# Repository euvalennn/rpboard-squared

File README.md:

# RPBoard²

RPBoard² is a simple RP2350-based board with multiple convenient features built-in. It's my first "actual" PCB project (I only did a hackpad before)

## Motivation

I wanted to build a devboard to learn more about actual PCB design and electronics, instead of using pre-made boards. I considered it as a personal challenge and ended up learning a lot on the two weeks it took me to make it :D

## Features:

- RP2350A MCU
- JST Debug header
- Built-in lithium battery support
- microSD card reader
- On-board RGB LED on GPIO25 (neopixel)
- QWIIC / Stemma QT I2C connector
- USB-C connector
- 16MB flash memory

## Built project:

| Front                                     | Back                                     |
| ----------------------------------------- | ---------------------------------------- |
|  |  |

## PCB and schematic:

### Schematic:

### PCB:

| PCB editor                                          | 3D viewer                                        |
| --------------------------------------------------- | ------------------------------------------------ |
|  |  |

Both the PCB and the schematic were designed using KiCad. The PCB is a 2-layer board with a ground pour on both layers.

## BOM:

| Name                             | Description                                                                                                                                            | Quantity | LCSC Part # | Total price |
| -------------------------------- | ------------------------------------------------------------------------------------------------------------------------------------------------------ | -------- | ----------- | ----------- |
| CL05A106MP5NUNC                  | 10V 10uF X5R ±20% 0402 Multilayer Ceramic Capacitors MLCC - SMD/SMT ROHS                                                                               | 4        | C315248     | $0.1640     |
| CGA0402X7R104K160GT              | 16V 100nF X7R ±10% 0402 Multilayer Ceramic Capacitors MLCC - SMD/SMT ROHS                                                                              | 13       | C6119799    | $0.0342     |
| CL05A475MP5NRNC                  | 10V 4.7uF X5R ±20% 0402 Multilayer Ceramic Capacitors MLCC - SMD/SMT ROHS                                                                              | 4        | C23733      | $0.0384     |
| CC0402JRNPO9BN150                | 50V 15pF NP0 ±5% 0402 Multilayer Ceramic Capacitors MLCC - SMD/SMT ROHS                                                                                | 2        | C106997     | $0.0220     |
| XL-1608SURC-06                   | 20mA 225mcd Water Clear op View Mount 620nm~630nm Red 120° 50mW 2.3V 0603 LED Indication - Discrete ROHS                                               | 1        | C965799     | $0.0620     |
| SK6812MINI-HS                    | SMD,3.5x3.7mm RGB LEDs(Built-in IC) ROHS                                                                                                               | 1        | C2922787    | $0.4665     |
| 1N5819WS                         | 40V 600mV@1A 1A SOD-323 Schottky Diodes ROHS                                                                                                           | 1        | C191023     | $0.0192     |
| TYPE-C-31-M-12                   | 5A 1 16P Female Type-C SMD USB Connectors ROHS                                                                                                         | 1        | C165948     | $0.3394     |
| BM03B-SRSS-TB(LF)(SN)            | 1x3P 3P SH Tin 3 -25℃~+85℃ 1A 1 1mm Copper Alloy Surface Mount,Vertical SMD,P=1mm Wire To Board Connector ROHS                                         | 1        | C160389     | $1.1070     |
| S2B-PH-SM4-TB(LF)(SN)            | 1x2P 2P PH Tin 2 -25℃~+85℃ 2A 1 2mm Copper Alloy Surface Mount, Right Angle SMD,P=2mm,Surface Mount,Right Angle Wire To Board Connector ROHS           | 1        | C295747     | $0.9295     |
| TF-01A                           | 1.85mm Connector and Ejector MicroSD Card (TF Card) Push-Push SMD SD Card / Memory Card Connector ROHS                                                 | 1        | C91145      | $0.3372     |
| BM04B-SRSS-TB(LF)(SN)            | 1x4P 4P SH Tin 4 -25℃~+85℃ 1A 1 1mm Copper Alloy Surface Mount,Vertical SMD,P=1mm Wire To Board Connector ROHS                                         | 1        | C160390     | $0.9105     |
| AOTA-B201610S3R3-101-T           | 0806 Power Inductors ROHS                                                                                                                              | 1        | C42411119   | $1.3680     |
| AO3401A                          | 30V 4.2A 120mΩ@2.5V 1.4W 1.3V@250uA 1 P-Channel SOT-23 MOSFETs ROHS                                                                                    | 1        | C347476     | $0.2990     |
| 0402WGF5101TCE                   | 62.5mW Thick Film Resistor 50V ±100ppm/℃ ±1% 5.1kΩ 0402 Chip Resistor - Surface Mount ROHS                                                             | 3        | C25905      | $0.0030     |
| 0402WGF1002TCE                   | 62.5mW Thick Film Resistor 50V ±100ppm/℃ ±1% 10kΩ 0402 Chip Resistor - Surface Mount ROHS                                                              | 3        | C25744      | $0.0030     |
| 0402WGF330JTCE                   | 62.5mW Thick Film Resistor 50V ±100ppm/℃ ±1% 33Ω 0402 Chip Resistor - Surface Mount ROHS                                                               | 1        | C25105      | $0.0010     |
| RC0402FR-0727RL                  | 62.5mW Thick Film Resistor 50V ±100ppm/℃ ±1% 27Ω 0402 Chip Resistor - Surface Mount ROHS                                                               | 2        | C138021     | $0.0120     |
| FRC0402J102 TS                   | 62.5mW Thick Film Resistor 50V ±100ppm/℃ ±5% 1kΩ 0402 Chip Resistor - Surface Mount ROHS                                                               | 4        | C2906899    | $0.0080     |
| TS-1088-AR02016                  | Without Bracket 50mA 4mm 100,000 Cycles 12V 1.6N 3mm 2mm Round Button Surface Mount,Vertical SPST SMD Tactile Switches ROHS                            | 2        | C720477     | $0.1692     |
| RP2350A                          | QFN-60-EP(7x7) Microcontrollers (MCU/MPU/SOC) ROHS                                                                                                     | 1        | C42411118   | $2.1330     |
| NCP1117ST33T3G                   | 62dB@(120Hz) 1A Fixed 3.3V Positive 20V SOT-223 Voltage Regulators - Linear, Low Drop Out (LDO) Regulators ROHS                                        | 1        | C26537      | $0.5098     |
| W25Q128JVSIQ                     | 128Mbit SPI 133MHz SOIC-8-208mil NOR FLASH ROHS                                                                                                        | 1        | C97521      | $1.9590     |
| TP4056-42-ESOP8                  | 4V~8V Lithium-ion/Polymer 1 1A ESOP-8 Battery Management ROHS                                                                                          | 1        | C16581      | $0.3438     |
| ABM8-272-T3                      | SMD3225-4P Crystals ROHS                                                                                                                               | 1        | C20625731   | $2.1000     |
| PCB Price                        | JLCPCB                                                                                                                                                 | 5        | N/A         | $2.00       |
| Economic PCBA setup fee          | JLCPCB                                                                                                                                                 | N/A      | N/A         | $8.00       |
| PCBA stencil                     | JLCPCB                                                                                                                                                 | N/A      | N/A         | $1.50       |
| Extended components fee          | JLCPCB                                                                                                                                                 | N/A      | N/A         | $51.00      |
| SMT assembly                     | JLCPCB                                                                                                                                                 | N/A      | N/A         | $1.13       |
| Special components fee           | JLCPCB                                                                                                                                                 | N/A      | N/A         | $0.06       |
| Nitrogen reflow soldering        | JLCPCB                                                                                                                                                 | N/A      | N/A         | $0.82       |
| Shipping to Argentina (cheapest) | DHL Express (FedEx appears to be cheaper on cart page but adds an additional remote area surcharge at checkout, DHL ends up being the cheapest option) | N/A      | N/A         | $33.33      |
| Subtotal                         | N/A                                                                                                                                                    | N/A      | N/A         | $111.18     |
| Total after $80 JLCPCB coupon    | N/A                                                                                                                                                    | N/A      | N/A         | $31.18      |

Although DHL shipping is expensive, it's the cheapest option for Argentina. FedEx has a cheaper price in the cart page, but after checking out it adds a $50+ remote area surcharge.

## Special thanks:

Thanks to Hack Club and the highway organizing team for all their efforts to make this possible. I would have never thought I'd be capable of something like this, yet highway gave me the motivation I needed to actually learn and design, and the funding to make it real.

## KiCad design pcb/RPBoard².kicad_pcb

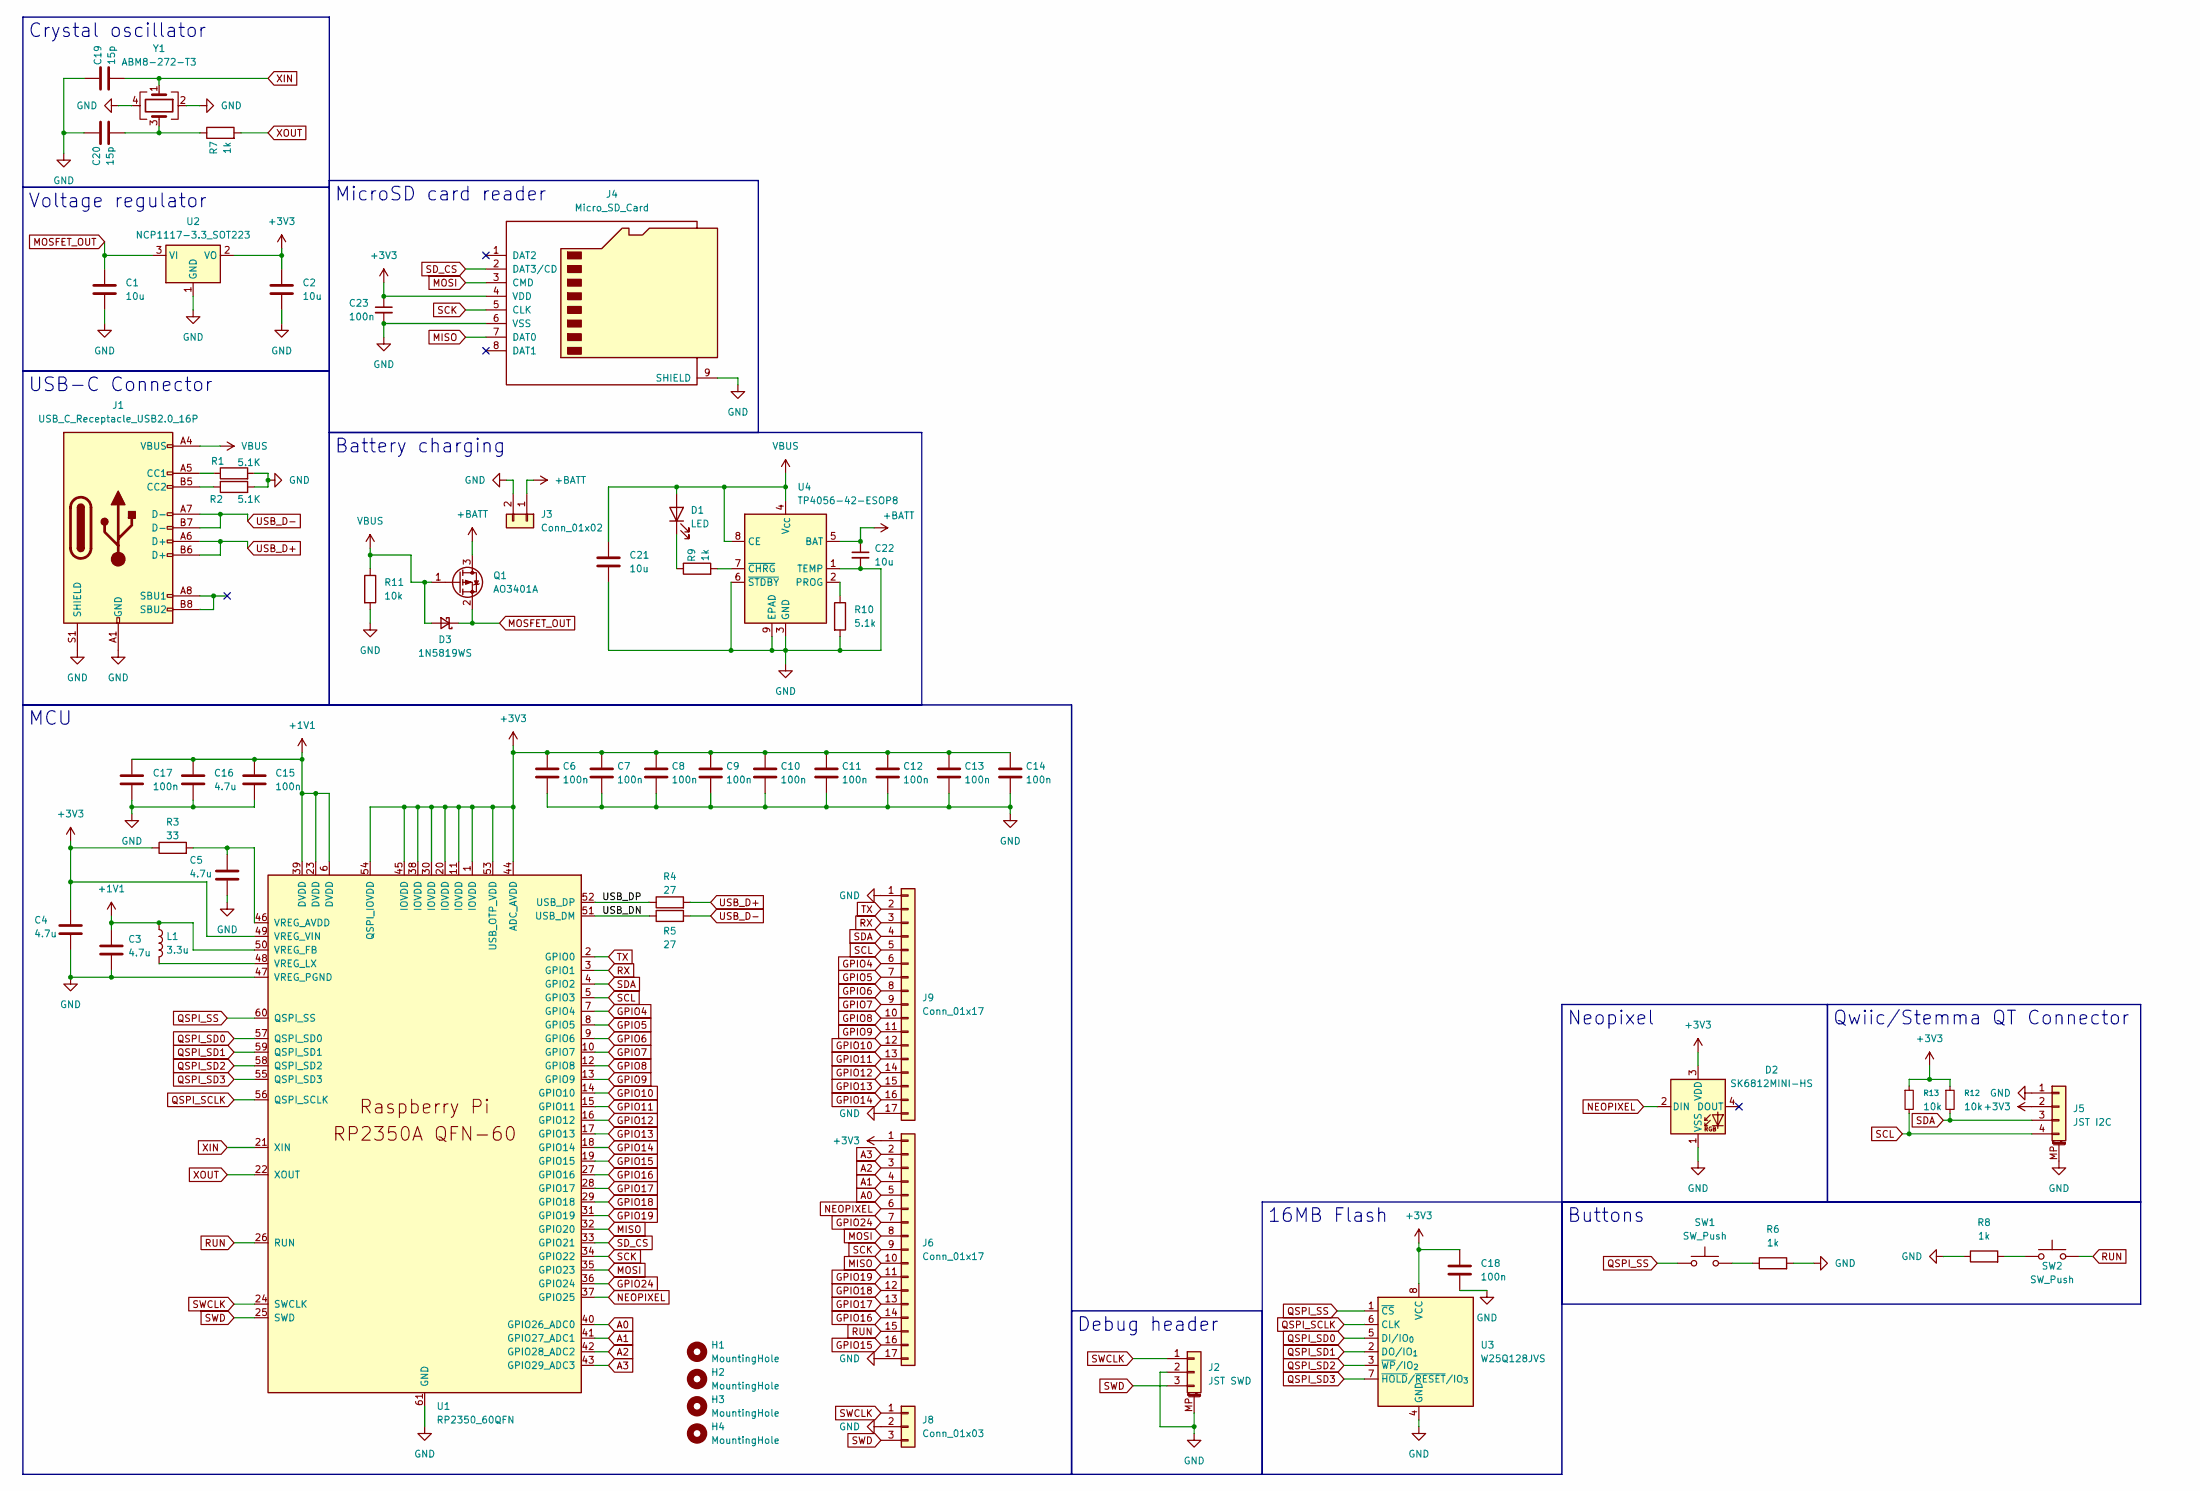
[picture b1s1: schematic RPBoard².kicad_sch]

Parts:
C1, C2, C21, C22: 10u; C_0402_1005Metric
C3, C4, C5, C16: 4.7u; C_0402_1005Metric
C6, C7, C8, C9, C10, C11, C12, C13, C14, C15, C17, C18, C23: 100n; C_0402_1005Metric
C19, C20: 15p; C_0402_1005Metric
D1: LED; LED_0603_1608Metric
D2: SK6812MINI-HS; LED_SK6812MINI_PLCC4_3.5x3.5mm_P1.75mm
D3: 1N5819WS; D_SOD-323
H1, H2, H3, H4: MountingHole; MountingHole_3.2mm_M3
J1: USB_C_Receptacle_USB2.0_16P; TYPE-C-31-M-12
J2: JST SWD; JST_SH_BM03B-SRSS-TB_1x03-1MP_P1.00mm_Vertical
J3: Conn_01x02; JST_PH_S2B-PH-SM4-TB_1x02-1MP_P2.00mm_Horizontal
J4: Micro_SD_Card; TF-01A
J5: JST I2C; JST_SH_BM04B-SRSS-TB_1x04-1MP_P1.00mm_Vertical
J6, J9: Conn_01x17; PinHeader_1x17_P2.54mm_Vertical
J8: Conn_01x03; PinHeader_1x03_P2.54mm_Vertical
L1: 3.3u; L_pol_2016
Q1: AO3401A; SOT-23
R1, R2: 5.1K; R_0402_1005Metric
R3: 33; R_0402_1005Metric
R4, R5: 27; R_0402_1005Metric
R6, R7, R8, R9: 1k; R_0402_1005Metric
R10: 5.1k; R_0402_1005Metric
R11, R12, R13: 10k; R_0402_1005Metric
SW1, SW2: SW_Push; TS-1088-ARXXX
U1: RP2350_60QFN; QFN-60-1EP_7x7mm_P0.4mm_EP3.4x3.4mm
U2: NCP1117-3.3_SOT223; SOT-223-3_TabPin2
U3: W25Q128JVS; SOIC-8_5.3x5.3mm_P1.27mm
U4: TP4056-42-ESOP8; SOIC-8-1EP_3.9x4.9mm_P1.27mm_EP2.41x3.3mm_ThermalVias
Y1: ABM8-272-T3; XTAL_ABM8-272-T3

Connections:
+1V1: C3.1, C15.1, C16.1, C17.1, L1.1, U1.6 (DVDD), U1.23 (DVDD), U1.39 (DVDD), U1.50 (VREG_FB)
+3V3: C2.1, C4.1, C6.1, C7.1, C8.1, C9.1, C10.1, C11.1, C12.1, C13.1, C14.1, C18.1, C23.1, D2.3 (VDD), J4.4 (VDD), J5.2, J6.1, R3.1, R12.1, R13.1, U1.1 (IOVDD), U1.11 (IOVDD), U1.20 (IOVDD), U1.30 (IOVDD), U1.38 (IOVDD), U1.44 (ADC_AVDD), U1.45 (IOVDD), U1.49 (VREG_VIN), U1.53 (USB_OTP_VDD), U1.54 (QSPI_IOVDD), U2.2 (VO), U3.8 (VCC)
+BATT: C22.1, J3.1, Q1.3 (D), U4.5 (BAT)
/USB_DN: R5.1, U1.51 (USB_DM)
/USB_DP: R4.1, U1.52 (USB_DP)
A0: J6.5, U1.40 (GPIO26_ADC0)
A1: J6.4, U1.41 (GPIO27_ADC1)
A2: J6.3, U1.42 (GPIO28_ADC2)
A3: J6.2, U1.43 (GPIO29_ADC3)
GND: C1.2, C2.2, C3.2, C4.2, C5.2, C6.2, C7.2, C8.2, C9.2, C10.2, C11.2, C12.2, C13.2, C14.2, C15.2, C16.2, C17.2, C18.2, C19.1, C20.1, C21.2, C22.2, C23.2, D2.1 (VSS), J1.A1 (GND), J1.A12 (GND), J1.B1 (GND), J1.B12 (GND), J1.S1 (SHIELD), J2.2, J2.MP (MountPin), J3.2, J4.6 (VSS), J4.9 (SHIELD), J5.1, J5.MP (MountPin), J6.17, J8.2, J9.1, J9.17, R1.2, R2.2, R6.2, R8.1, R10.2, R11.2, U1.47 (VREG_PGND), U1.61 (GND), U2.1 (GND), U3.4 (GND), U4.1 (TEMP), U4.3 (GND), U4.6 (~STDBY), U4.9 (EPAD), Y1.2, Y1.4
GPIO4: J9.6, U1.7 (GPIO4)
GPIO5: J9.7, U1.8 (GPIO5)
GPIO6: J9.8, U1.9 (GPIO6)
GPIO7: J9.9, U1.10 (GPIO7)
GPIO8: J9.10, U1.12 (GPIO8)
GPIO9: J9.11, U1.13 (GPIO9)
GPIO10: J9.12, U1.14 (GPIO10)
GPIO11: J9.13, U1.15 (GPIO11)
GPIO12: J9.14, U1.16 (GPIO12)
GPIO13: J9.15, U1.17 (GPIO13)
GPIO14: J9.16, U1.18 (GPIO14)
GPIO15: J6.16, U1.19 (GPIO15)
GPIO16: J6.14, U1.27 (GPIO16)
GPIO17: J6.13, U1.28 (GPIO17)
GPIO18: J6.12, U1.29 (GPIO18)
GPIO19: J6.11, U1.31 (GPIO19)
GPIO24: J6.7, U1.36 (GPIO24)
MISO: J4.7 (DAT0), J6.10, U1.32 (GPIO20)
MOSFET_OUT: C1.1, D3.1 (K), Q1.2 (S), U2.3 (VI)
MOSI: J4.3 (CMD), J6.8, U1.35 (GPIO23)
NEOPIXEL: D2.2 (DIN), J6.6, U1.37 (GPIO25)
unnamed: C20.2, R7.1, Y1.3
unnamed: D1.1 (K), R9.1
unnamed: J1.A5 (CC1), R1.1
unnamed: J1.B5 (CC2), R2.1
unnamed: R6.1, SW1.2
unnamed: R8.2, SW2.1
unnamed: C5.1, R3.2, U1.46 (VREG_AVDD)
unnamed: L1.2, U1.48 (VREG_LX)
unnamed: R10.1, U4.2 (PROG)
unnamed: R9.2, U4.7 (~CHRG)
QSPI_SCLK: U1.56 (QSPI_SCLK), U3.6 (CLK)
QSPI_SD0: U1.57 (QSPI_SD0), U3.5 (DI/IO_{0})
QSPI_SD1: U1.59 (QSPI_SD1), U3.2 (DO/IO_{1})
QSPI_SD2: U1.58 (QSPI_SD2), U3.3 (~WP/IO_{2})
QSPI_SD3: U1.55 (QSPI_SD3), U3.7 (~HOLD/~RESET/IO_{3})
QSPI_SS: SW1.1, U1.60 (QSPI_SS), U3.1 (~CS)
RUN: J6.15, SW2.2, U1.26 (RUN)
RX: J9.3, U1.3 (GPIO1)
SCK: J4.5 (CLK), J6.9, U1.34 (GPIO22)
SCL: J5.4, J9.5, R13.2, U1.5 (GPIO3)
SDA: J5.3, J9.4, R12.2, U1.4 (GPIO2)
SD_CS: J4.2 (DAT3/CD), U1.33 (GPIO21)
SWCLK: J2.1, J8.1, U1.24 (SWCLK)
SWD: J2.3, J8.3, U1.25 (SWD)
TX: J9.2, U1.2 (GPIO0)
USB_D+: J1.A6 (D+), J1.B6 (D+), R4.2
USB_D-: J1.A7 (D-), J1.B7 (D-), R5.2
VBUS: C21.1, D1.2 (A), D3.2 (A), J1.A4 (VBUS), J1.A9 (VBUS), J1.B4 (VBUS), J1.B9 (VBUS), Q1.1 (G), R11.1, U4.4 (V_{CC}), U4.8 (CE)
XIN: C19.2, U1.21 (XIN), Y1.1
XOUT: R7.2, U1.22 (XOUT)

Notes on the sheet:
MCU
16MB Flash
Crystal oscillator
Buttons
Voltage regulator
Qwiic/Stemma QT Connector
MicroSD card reader
USB-C Connector
Battery charging
Neopixel
Debug header

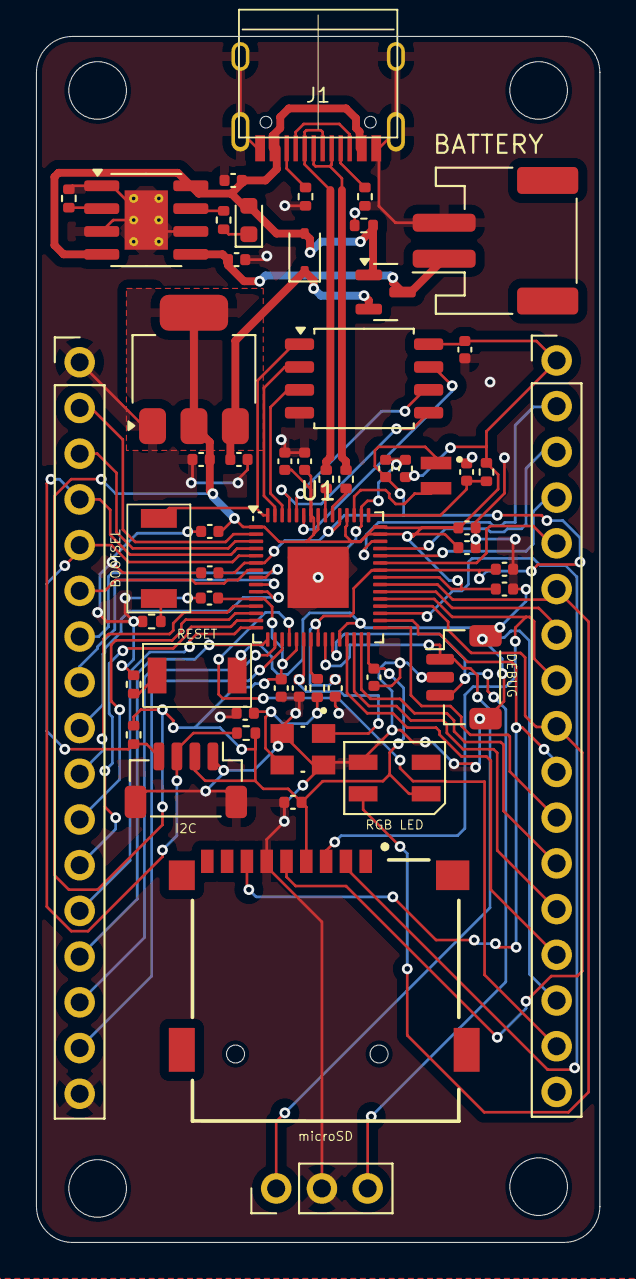
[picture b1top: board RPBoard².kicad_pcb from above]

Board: 2 copper layers, 31.3 x 67.0 mm, 60 parts (0 on the bottom side), 61 nets.

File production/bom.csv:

Designator,Footprint,Quantity,Value,LCSC Part #
"C1, C2, C21, C22",0402,4,10u,C315248
"C10, C11, C12, C13, C14, C15, C17, C18, C23, C6, C7, C8, C9",0402,13,100n,C6119799
"C16, C3, C4, C5",0402,4,4.7u,C23733
"C19, C20",0402,2,15p,C106997
D1,0603,1,LED,C965799
D2,LED_SK6812MINI_PLCC4_3.5x3.5mm_P1.75mm,1,SK6812MINI-HS,C2922787
D3,D_SOD-323,1,1N5819WS,C191023
J1,TYPE-C-31-M-12,1,USB_C_Receptacle_USB2.0_16P,C165948
J2,JST_SH_BM03B-SRSS-TB_1x03-1MP_P1.00mm_Vertical,1,JST SWD,C160389
J3,JST_PH_S2B-PH-SM4-TB_1x02-1MP_P2.00mm_Horizontal,1,Conn_01x02,C295747
J4,TF-01A,1,Micro_SD_Card,C91145
J5,JST_SH_BM04B-SRSS-TB_1x04-1MP_P1.00mm_Vertical,1,JST I2C,C160390
L1,L_pol_2016,1,3.3u,C42411119
Q1,SOT-23,1,AO3401A,C347476
"R1, R10, R2",0402,3,5.1K,C25905
"R11, R12, R13",0402,3,10k,C25744
R3,0402,1,33,C25105
"R4, R5",0402,2,27,C138021
"R6, R7, R8, R9",0402,4,1k,C2906899
"SW1, SW2",TS-1088-ARXXX,2,SW_Push,C720477
U1,QFN-60-1EP_7x7mm_P0.4mm_EP3.4x3.4mm,1,RP2350_60QFN,C42411118
U2,SOT-223-3_TabPin2,1,NCP1117-3.3_SOT223,C26537
U3,SOIC-8_5.3x5.3mm_P1.27mm,1,W25Q128JVS,C97521
U4,SOIC-8-1EP_3.9x4.9mm_P1.27mm_EP2.41x3.3mm_ThermalVias,1,TP4056-42-ESOP8,C16581
Y1,XTAL_ABM8-272-T3,1,ABM8-272-T3,C20625731

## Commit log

2025-07-16 added july 15 journal entry
2025-07-17 added july 16 journal entry
2025-07-18 added july 17 journal entry
2025-07-22 added july 18 journal entry
2025-07-24 added july 22 journal entry
2025-07-25 added july 24 journal entry
2025-07-27 added july 25 journal entry
2025-07-29 added july 27 journal entry
2025-07-30 added july 29 journal entry and all project files
2025-08-25 updated PCB image in readme
2025-08-25 updated journal
2025-08-25 updated gerbers to add thermal vias
2025-08-25 updated firmware, only thing changed is neopixel color
2025-08-25 added build photos to readme
2025-09-09 added built project images to journal
2026-06-14 removed broken image from readme
